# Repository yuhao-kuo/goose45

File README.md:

# Goose45

Goose45 is a 45% keyboard project.

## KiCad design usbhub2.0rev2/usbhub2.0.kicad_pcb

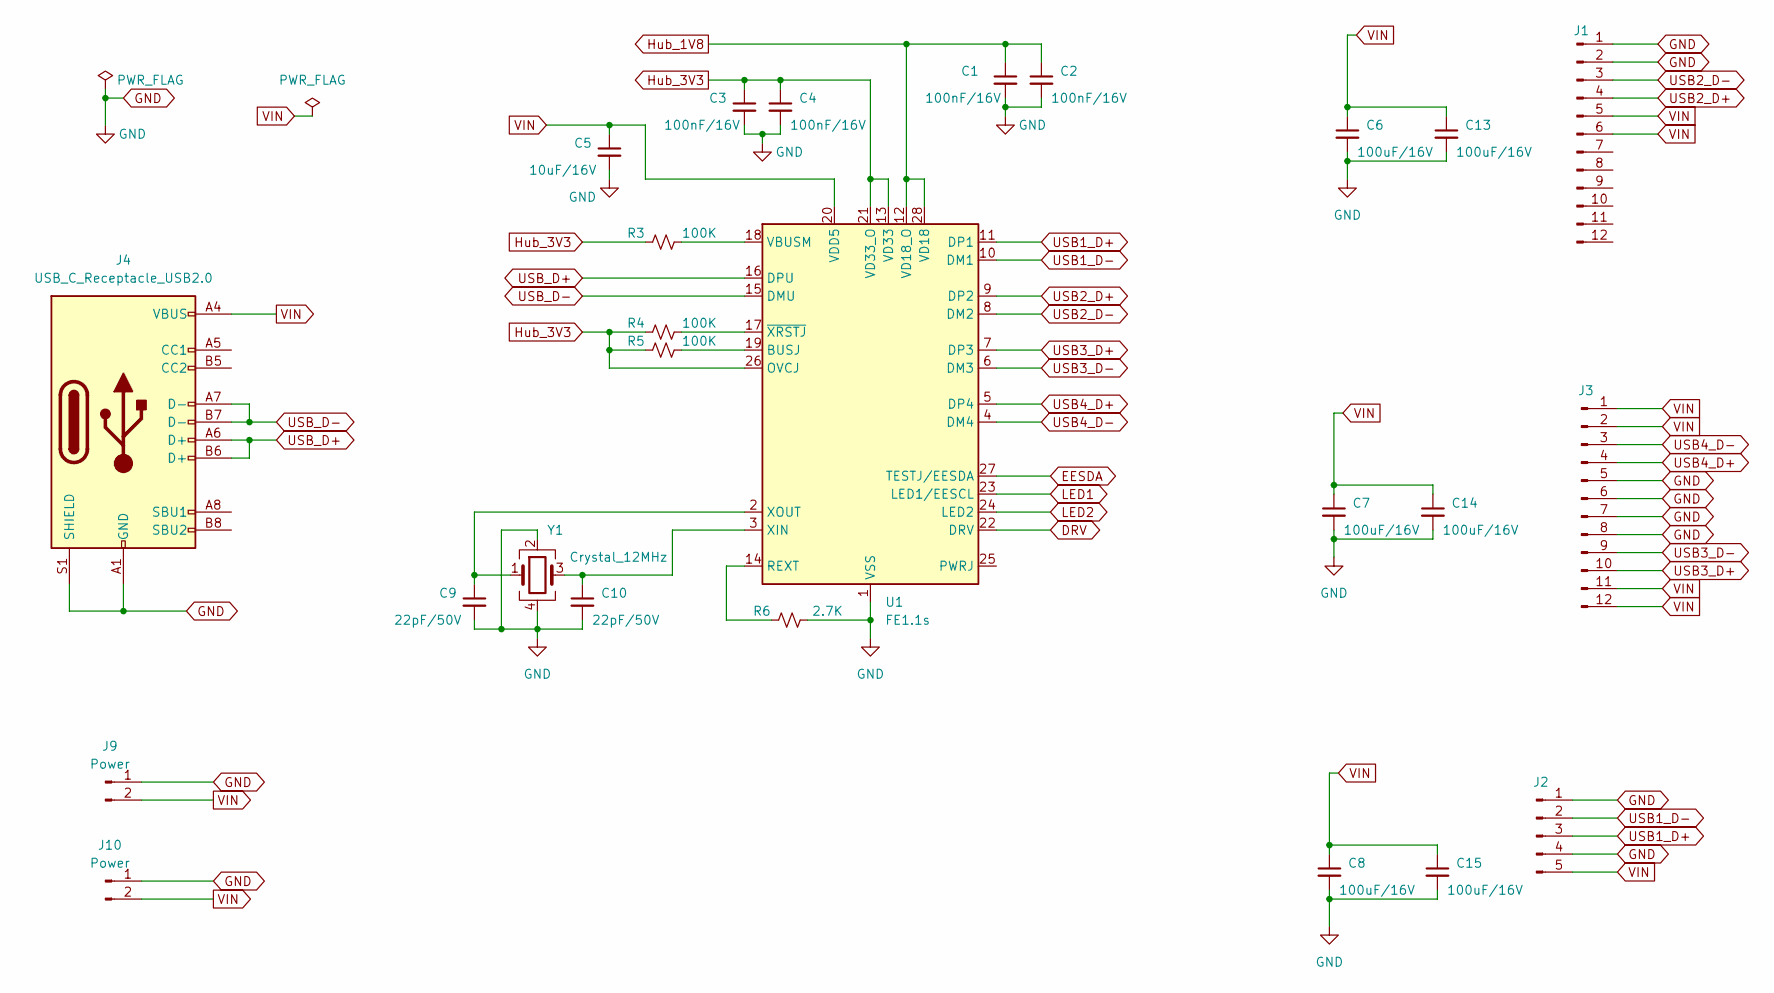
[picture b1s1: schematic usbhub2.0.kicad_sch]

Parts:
C1, C2, C3, C4: 100nF/16V; C_0603_1608Metric
C5: 10uF/16V; C_0603_1608Metric
C6, C7, C8: 100uF/16V; C_1206_3216Metric
C9, C10: 22pF/50V; C_0603_1608Metric
C13, C14, C15: 100uF/16V; CP_EIA-7343-30_AVX-N_Pad2.25x2.55mm_HandSolder
J1, J3: Conn_01x12_Pin; Hirose_FH12-12S-0.5SH_1x12-1MP_P0.50mm_Horizontal
J2: Conn_01x05_Male; PinHeader_1x05_P2.54mm_Vertical
J4: USB_C_Receptacle_USB2.0; USB_C_Receptacle_HRO_TYPE-C-31-M-12
J9, J10: Power; PinHeader_1x02_P2.54mm_Vertical
R3, R4, R5: 100K; R_0603_1608Metric
R6: 2.7K; R_0603_1608Metric
U1: FE1.1s; SSOP-28_3.9x9.9mm_P0.635mm
Y1: Crystal_12MHz; Crystal_SMD_Abracon_ABM3C-4Pin_5.0x3.2mm

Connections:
DRV: U1.22 (DRV)
EESDA: U1.27 (TESTJ/EESDA)
GND: C1.2, C2.2, C3.2, C4.2, C5.2, C6.2, C7.2, C8.2, C9.2, C10.2, C13.2, C14.2, C15.2, J1.1, J1.2, J2.1, J2.4, J3.5, J3.6, J3.7, J3.8, J4.A1 (GND), J4.A12 (GND), J4.B1 (GND), J4.B12 (GND), J4.S1 (SHIELD), J9.1, J10.1, R6.2, U1.1 (VSS), Y1.2, Y1.4
Hub_1V8: C1.1, C2.1, U1.12 (VD18_O), U1.28 (VD18)
Hub_3V3: C3.1, C4.1, R3.1, R4.1, R5.1, U1.13 (VD33), U1.21 (VD33_O), U1.26 (OVCJ)
LED1: U1.23 (LED1/EESCL)
LED2: U1.24 (LED2)
unnamed: R5.2, U1.19 (BUSJ)
unnamed: R6.1, U1.14 (REXT)
unnamed: R3.2, U1.18 (VBUSM)
unnamed: C10.1, U1.3 (XIN), Y1.3
unnamed: C9.1, U1.2 (XOUT), Y1.1
unnamed: R4.2, U1.17 (~XRSTJ)
USB1_D+: J2.3, U1.11 (DP1)
USB1_D-: J2.2, U1.10 (DM1)
USB2_D+: J1.4, U1.9 (DP2)
USB2_D-: J1.3, U1.8 (DM2)
USB3_D+: J3.10, U1.7 (DP3)
USB3_D-: J3.9, U1.6 (DM3)
USB4_D+: J3.4, U1.5 (DP4)
USB4_D-: J3.3, U1.4 (DM4)
USB_D+: J4.A6 (D+), J4.B6 (D+), U1.16 (DPU)
USB_D-: J4.A7 (D-), J4.B7 (D-), U1.15 (DMU)
VIN: C5.1, C6.1, C7.1, C8.1, C13.1, C14.1, C15.1, J1.5, J1.6, J2.5, J3.1, J3.2, J3.11, J3.12, J4.A4 (VBUS), J4.A9 (VBUS), J4.B4 (VBUS), J4.B9 (VBUS), J9.2, J10.2, U1.20 (VDD5)

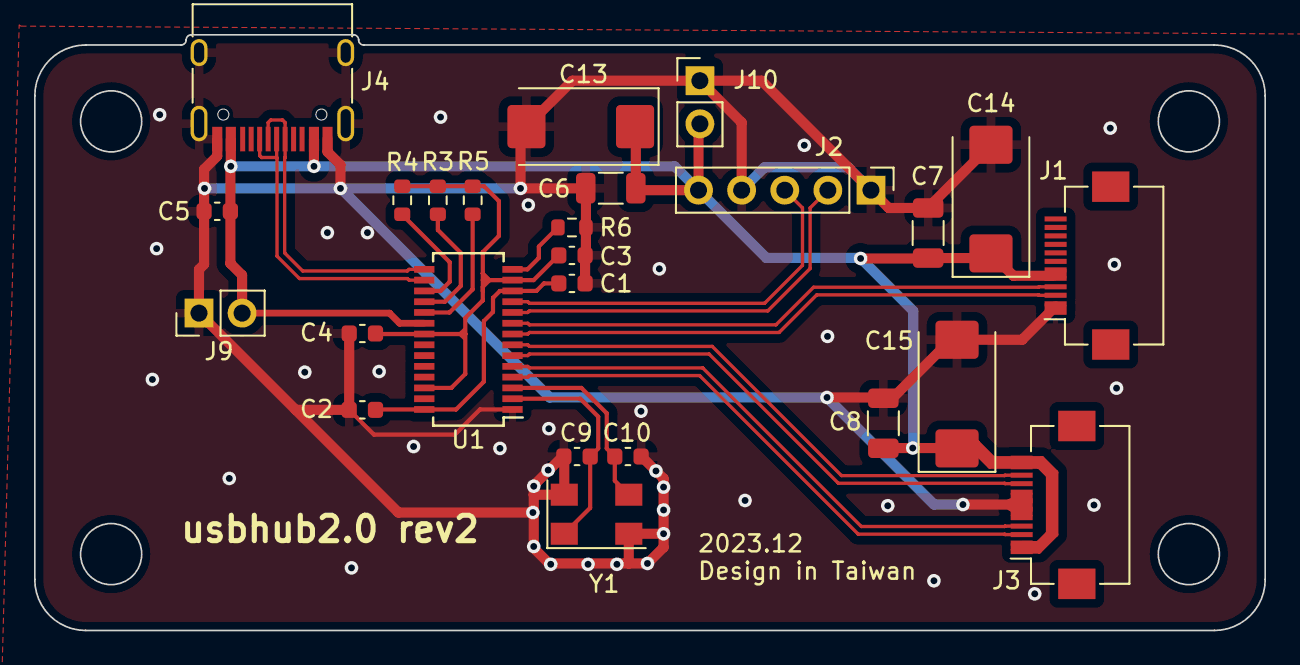
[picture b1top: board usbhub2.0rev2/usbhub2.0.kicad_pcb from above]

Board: 2 copper layers, 72.5 x 35.1 mm, 25 parts (0 on the bottom side), 20 nets.

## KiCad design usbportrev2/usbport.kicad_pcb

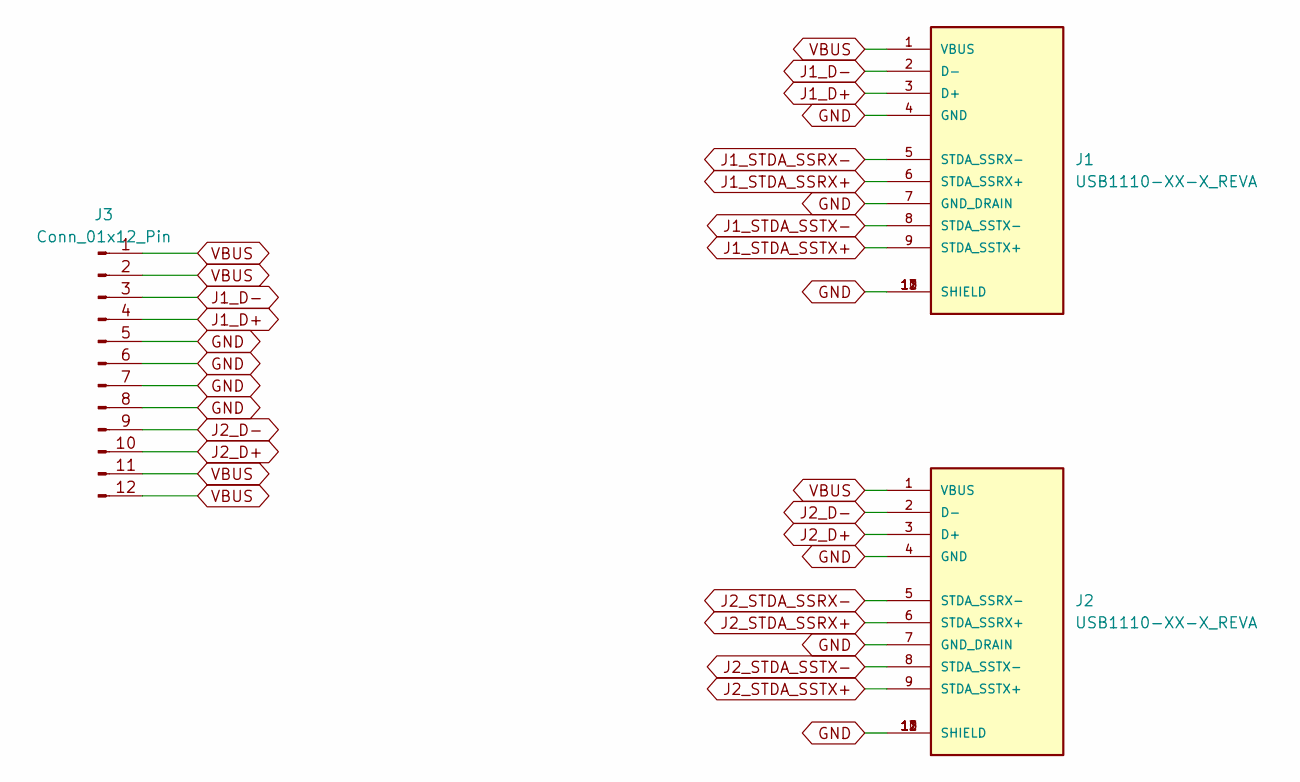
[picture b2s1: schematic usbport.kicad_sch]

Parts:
J1, J2: USB1110-XX-X_REVA; GCT_USB1110_goose45_usbport
J3: Conn_01x12_Pin; Hirose_FH12-12S-0.5SH_1x12-1MP_P0.50mm_Horizontal

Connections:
GND: J1.4 (GND), J1.7 (GND_DRAIN), J1.10 (SHIELD), J1.11 (SHIELD), J1.12 (SHIELD), J1.13 (SHIELD), J2.4 (GND), J2.7 (GND_DRAIN), J2.10 (SHIELD), J2.11 (SHIELD), J2.12 (SHIELD), J2.13 (SHIELD), J3.5, J3.6, J3.7, J3.8
J1_D+: J1.3 (D+), J3.4
J1_D-: J1.2 (D-), J3.3
J1_STDA_SSRX+: J1.6 (STDA_SSRX+)
J1_STDA_SSRX-: J1.5 (STDA_SSRX-)
J1_STDA_SSTX+: J1.9 (STDA_SSTX+)
J1_STDA_SSTX-: J1.8 (STDA_SSTX-)
J2_D+: J2.3 (D+), J3.10
J2_D-: J2.2 (D-), J3.9
J2_STDA_SSRX+: J2.6 (STDA_SSRX+)
J2_STDA_SSRX-: J2.5 (STDA_SSRX-)
J2_STDA_SSTX+: J2.9 (STDA_SSTX+)
J2_STDA_SSTX-: J2.8 (STDA_SSTX-)
VBUS: J1.1 (VBUS), J2.1 (VBUS), J3.1, J3.2, J3.11, J3.12

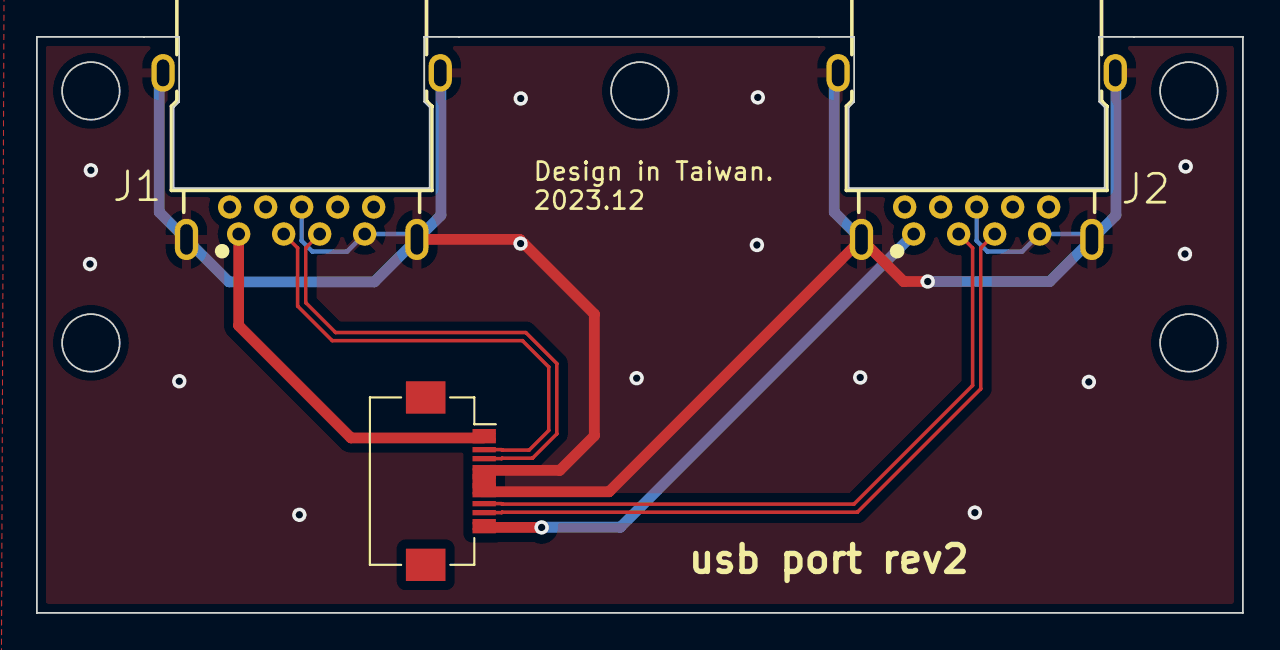
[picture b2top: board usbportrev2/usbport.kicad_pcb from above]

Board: 2 copper layers, 67.0 x 32.0 mm, 3 parts (0 on the bottom side), 6 nets.

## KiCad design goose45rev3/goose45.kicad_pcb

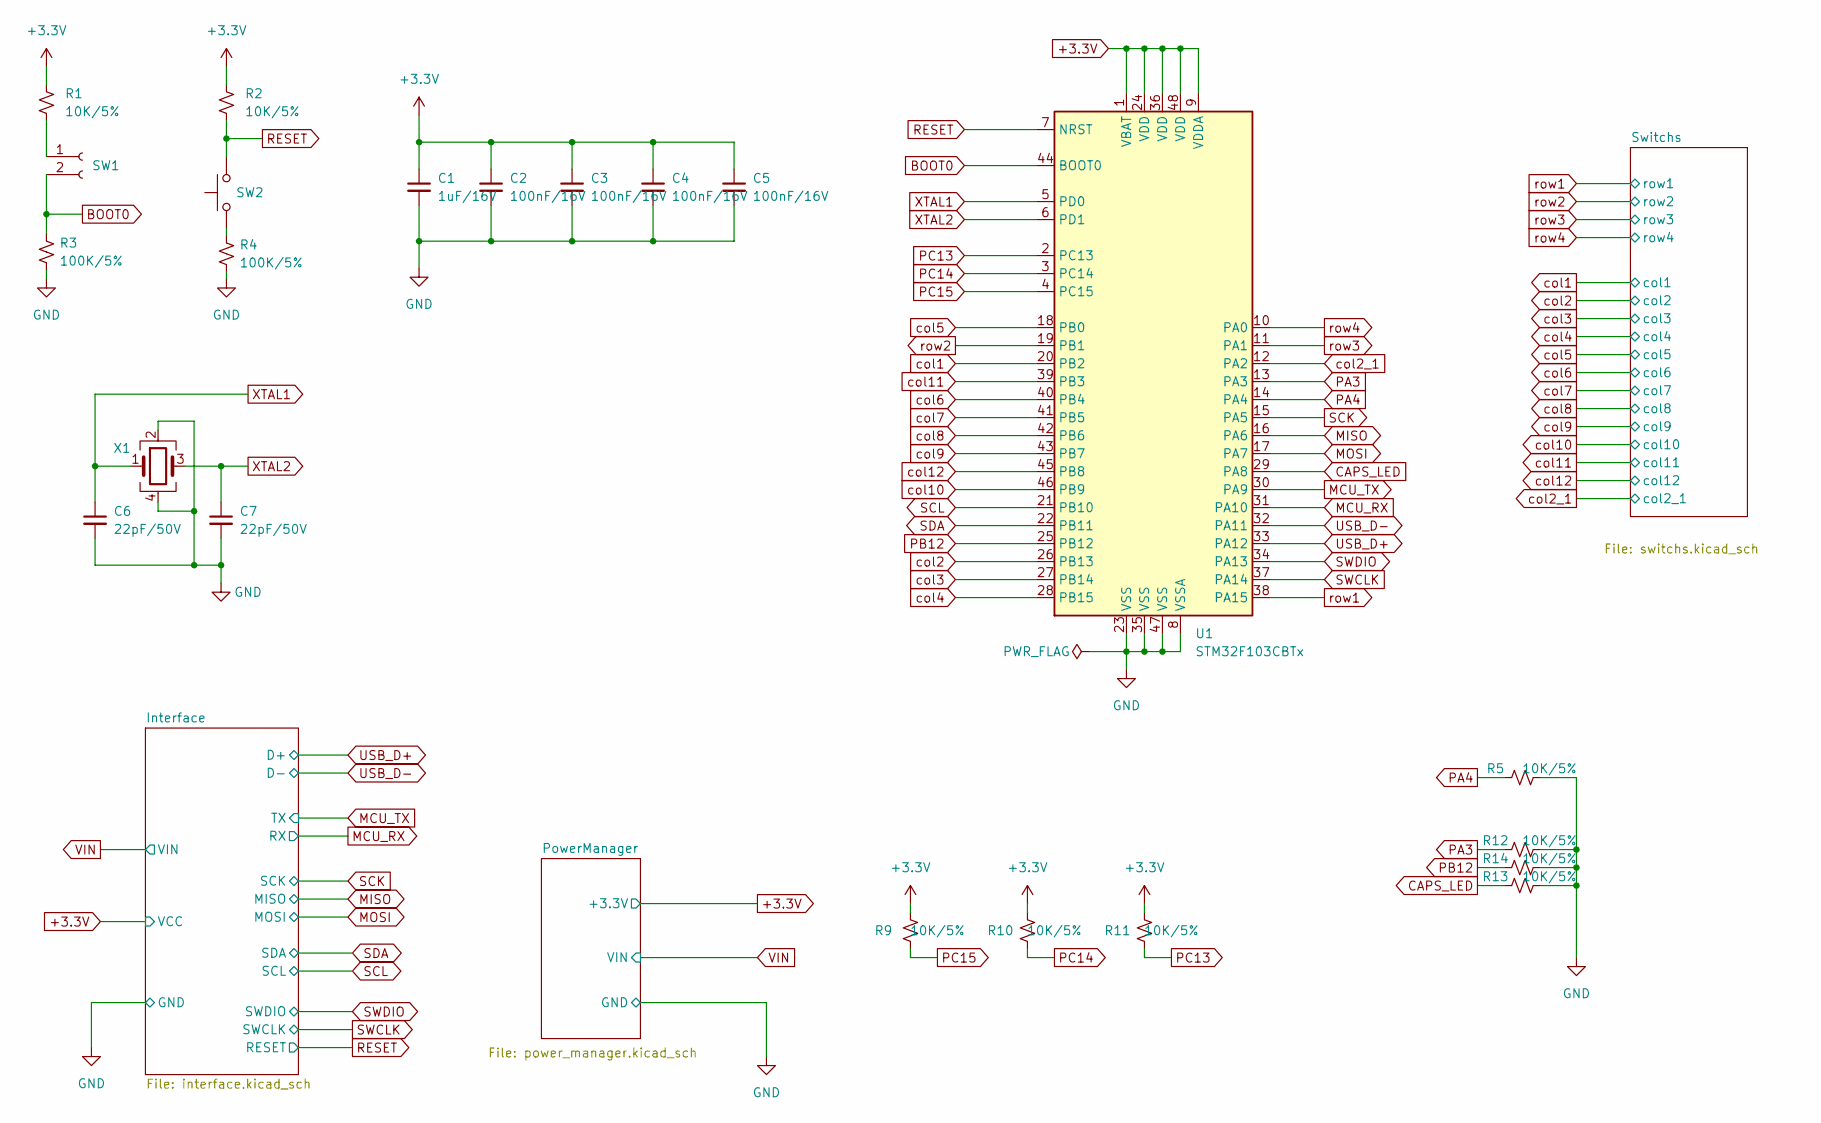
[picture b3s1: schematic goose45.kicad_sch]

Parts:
C1: 1uF/16V; C_0603_1608Metric
C2, C3, C4, C5: 100nF/16V; C_0603_1608Metric
C6, C7: 22pF/50V; C_0603_1608Metric
R1, R2, R5, R9, R10, R11, R12, R13, R14: 10K/5%; R_0603_1608Metric
R3, R4: 100K/5%; R_0603_1608Metric
SW1: Conn_01x02_Female; PinHeader_1x02_P2.00mm_Vertical
SW2: SW_Push; SW_Push_1P1T_NO_CK_KSC6xxJ
U1: STM32F103CBTx; LQFP-48_7x7mm_P0.5mm
X1: Crystal_GND24; Crystal_SMD_TXC_7M-4Pin_3.2x2.5mm

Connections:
+3.3V: C1.1, C2.1, C3.1, C4.1, C5.1, R1.1, R2.1, R9.1, R10.1, R11.1, U1.1 (VBAT), U1.9 (VDDA), U1.24 (VDD), U1.36 (VDD), U1.48 (VDD); also elsewhere on the board
BOOT0: R3.1, SW1.2, U1.44 (BOOT0)
CAPS_LED: R13.2, U1.29 (PA8)
GND: C1.2, C2.2, C3.2, C4.2, C5.2, C6.2, C7.2, R3.2, R4.2, R5.1, R12.1, R13.1, R14.1, U1.8 (VSSA), U1.23 (VSS), U1.35 (VSS), U1.47 (VSS), X1.2, X1.4; also elsewhere on the board
MCU_RX: U1.31 (PA10); also elsewhere on the board
MCU_TX: U1.30 (PA9); also elsewhere on the board
MISO: U1.16 (PA6); also elsewhere on the board
MOSI: U1.17 (PA7); also elsewhere on the board
unnamed: R4.1, SW2.1
unnamed: R1.2, SW1.1
PA3: R12.2, U1.13 (PA3)
PA4: R5.2, U1.14 (PA4)
PB12: R14.2, U1.25 (PB12)
PC13: R11.2, U1.2 (PC13)
PC14: R10.2, U1.3 (PC14)
PC15: R9.2, U1.4 (PC15)
RESET: R2.2, SW2.2, U1.7 (NRST); also elsewhere on the board
SCK: U1.15 (PA5); also elsewhere on the board
SCL: U1.21 (PB10); also elsewhere on the board
SDA: U1.22 (PB11); also elsewhere on the board
SWCLK: U1.37 (PA14); also elsewhere on the board
SWDIO: U1.34 (PA13); also elsewhere on the board
USB_D+: U1.33 (PA12); also elsewhere on the board
USB_D-: U1.32 (PA11); also elsewhere on the board
XTAL1: C6.1, U1.5 (PD0), X1.1
XTAL2: C7.1, U1.6 (PD1), X1.3
col1: U1.20 (PB2); also elsewhere on the board
col4: U1.28 (PB15); also elsewhere on the board
col5: U1.18 (PB0); also elsewhere on the board
col6: U1.40 (PB4); also elsewhere on the board
col7: U1.41 (PB5); also elsewhere on the board
col8: U1.42 (PB6); also elsewhere on the board
col10: U1.46 (PB9); also elsewhere on the board
col11: U1.39 (PB3); also elsewhere on the board
col12: U1.45 (PB8); also elsewhere on the board
row1: U1.38 (PA15); also elsewhere on the board
row2: U1.19 (PB1); also elsewhere on the board
row3: U1.11 (PA1); also elsewhere on the board
row4: U1.10 (PA0); also elsewhere on the board

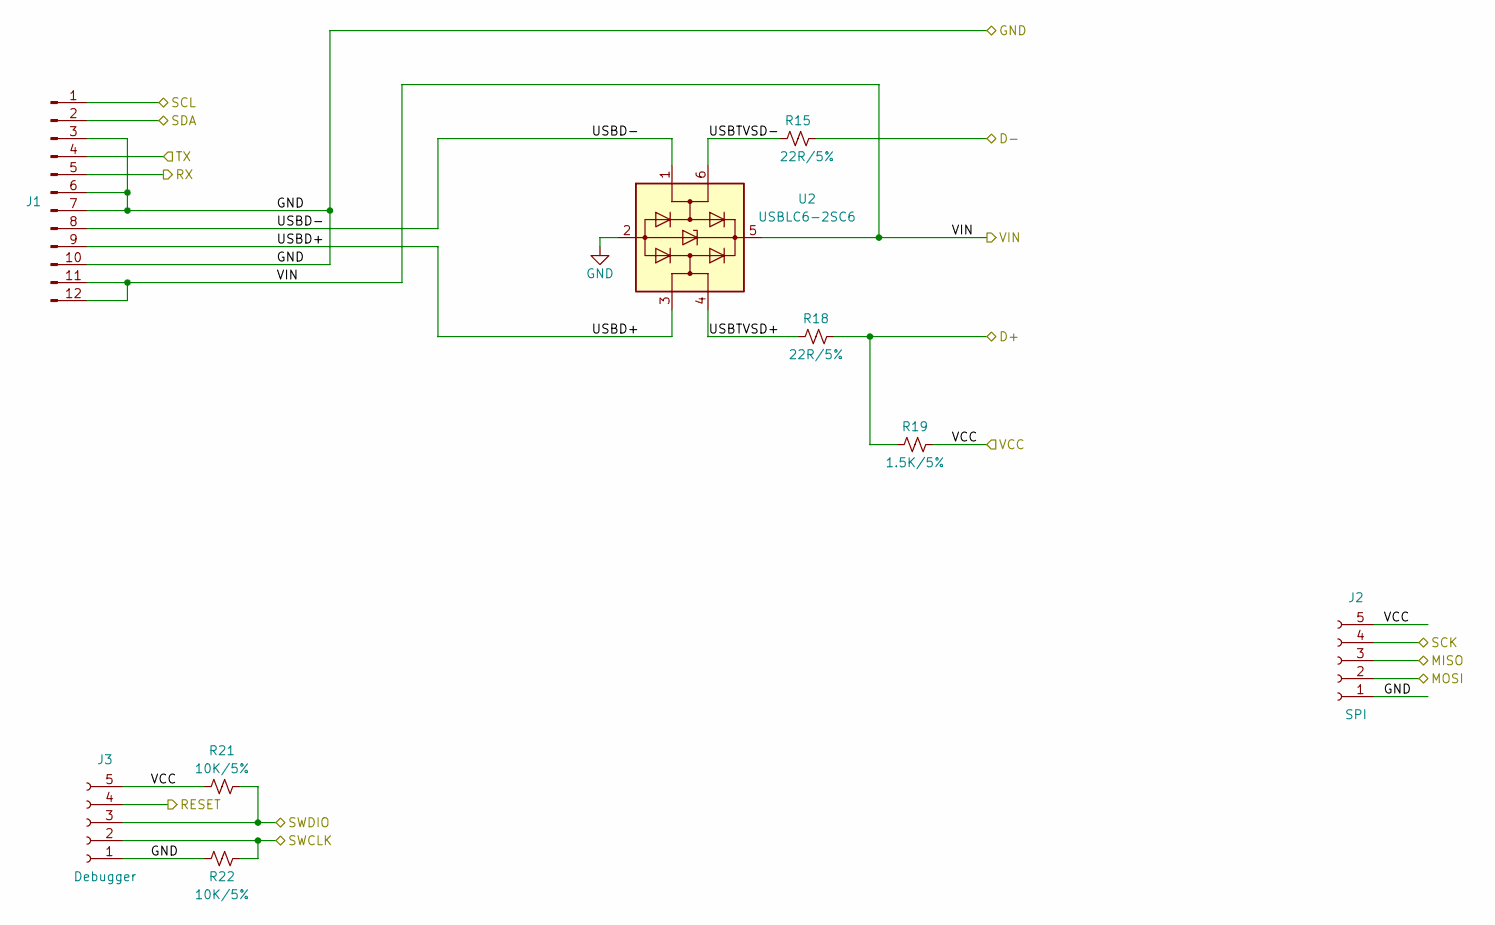
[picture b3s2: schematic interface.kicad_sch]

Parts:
J1: USB connector; Hirose_FH12-12S-0.5SH_1x12-1MP_P0.50mm_Horizontal
J2: SPI; PinHeader_1x05_P2.00mm_Vertical
J3: Debugger; PinHeader_1x05_P2.00mm_Vertical
R15, R18: 22R/5%; R_0603_1608Metric
R19: 1.5K/5%; R_0603_1608Metric
R21, R22: 10K/5%; R_0603_1608Metric
U2: USBLC6-2SC6; SOT-23-6

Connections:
+3.3V: J2.5, J3.5, R19.2, R21.1; also elsewhere on the board
/Interface/USBD+: J1.9, U2.3 (I/O2)
/Interface/USBD-: J1.8, U2.1 (I/O1)
/Interface/USBTVSD+: R18.1, U2.4 (I/O2)
/Interface/USBTVSD-: R15.1, U2.6 (I/O1)
GND: J1.3, J1.6, J1.7, J1.10, J2.1, J3.1, R22.1, U2.2 (GND); also elsewhere on the board
MCU_RX: J1.5; also elsewhere on the board
MCU_TX: J1.4; also elsewhere on the board
MISO: J2.3; also elsewhere on the board
MOSI: J2.2; also elsewhere on the board
RESET: J3.4; also elsewhere on the board
SCK: J2.4; also elsewhere on the board
SCL: J1.1; also elsewhere on the board
SDA: J1.2; also elsewhere on the board
SWCLK: J3.2, R22.2; also elsewhere on the board
SWDIO: J3.3, R21.2; also elsewhere on the board
USB_D+: R18.2, R19.1; also elsewhere on the board
USB_D-: R15.2; also elsewhere on the board
VIN: J1.11, J1.12, U2.5 (VBUS); also elsewhere on the board

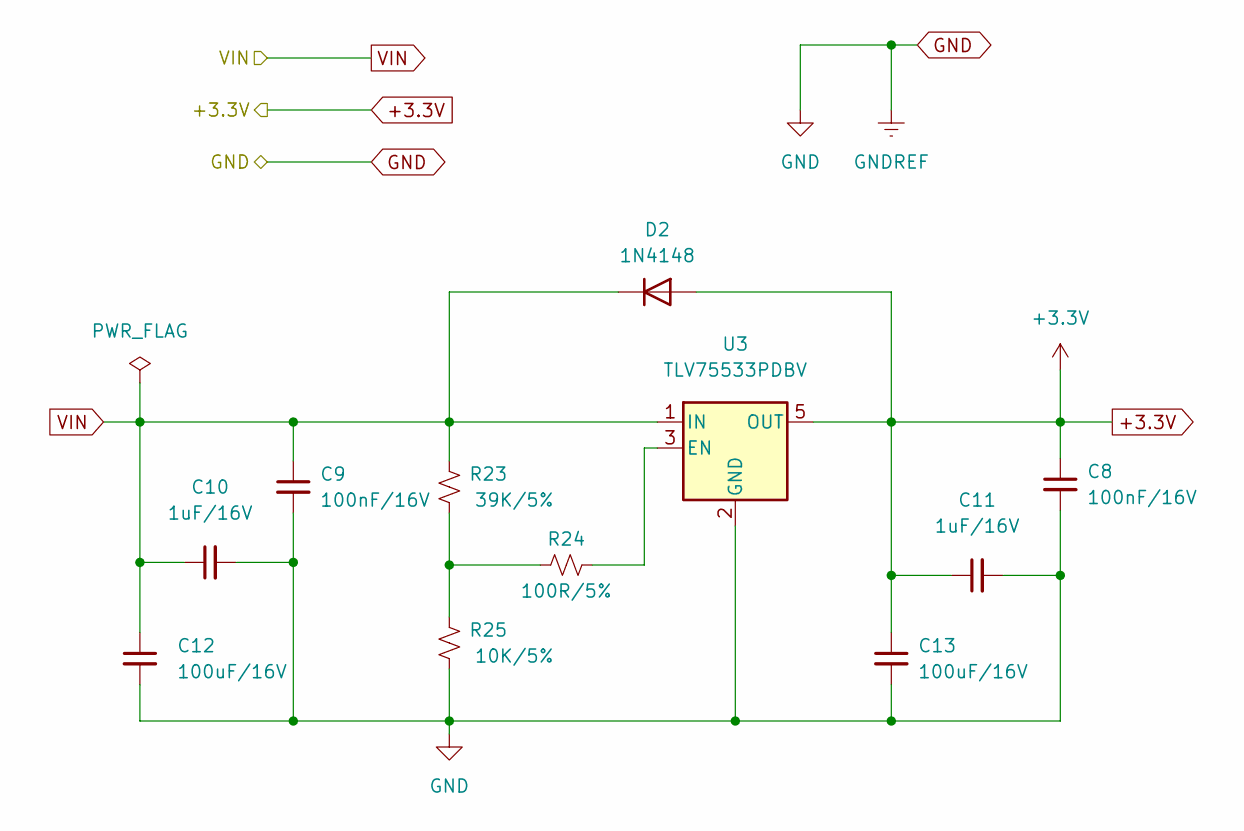
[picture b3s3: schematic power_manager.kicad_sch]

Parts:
C8, C9: 100nF/16V; C_0603_1608Metric
C10, C11: 1uF/16V; C_0603_1608Metric
C12, C13: 100uF/16V; C_0603_1608Metric
D2: 1N4148; D_SOD-323
R23: 39K/5%; R_0603_1608Metric
R24: 100R/5%; R_0603_1608Metric
R25: 10K/5%; R_0603_1608Metric
U3: TLV75533PDBV; SOT-23-5

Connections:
+3.3V: C8.1, C11.1, C13.1, D2.2 (A), U3.5 (OUT); also elsewhere on the board
GND: C8.2, C9.2, C10.2, C11.2, C12.2, C13.2, R25.2, U3.2 (GND); also elsewhere on the board
unnamed: R23.1, R24.2, R25.1
unnamed: R24.1, U3.3 (EN)
VIN: C9.1, C10.1, C12.1, D2.1 (K), R23.2, U3.1 (IN); also elsewhere on the board

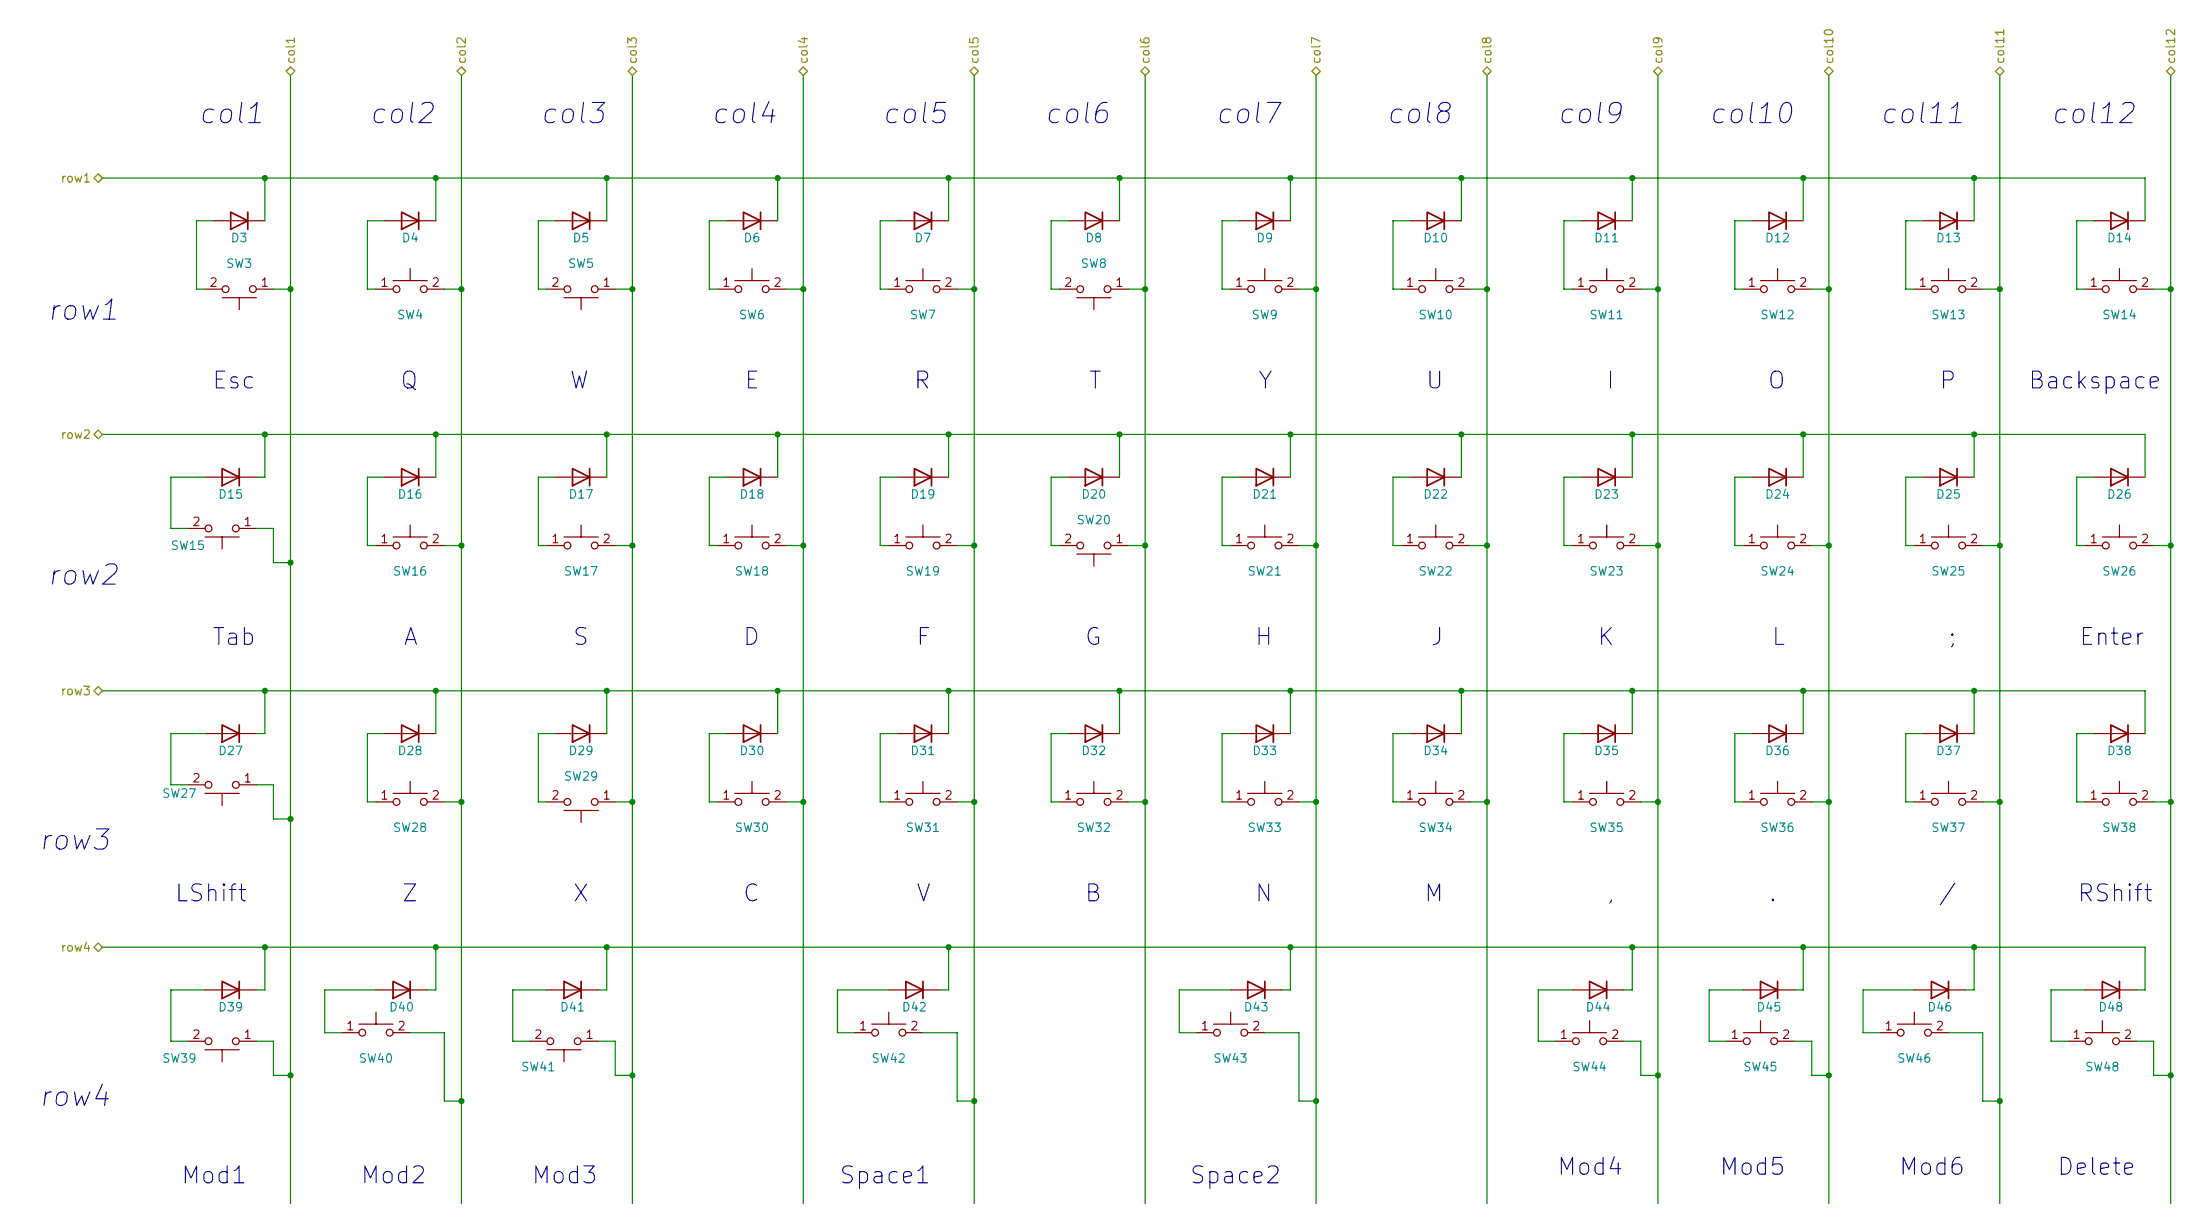
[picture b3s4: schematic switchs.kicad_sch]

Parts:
D3, D4, D5, D6, D7, D8, D9, D10, D11, D12, D13, D14, D15, D16, D17, D18, D19, D20, D21, D22, D23, D24, D25, D26, D27, D28, D29, D30, D31, D32, D33, D34, D35, D36, D37, D38, D39, D40, D41, D42, D43, D44, D45, D46, D48: 1N4148; D_0805_2012Metric
SW3, SW4, SW5, SW6, SW7, SW8, SW9, SW10, SW11, SW12, SW13, SW14, SW15, SW16, SW17, SW18, SW19, SW20, SW21, SW22, SW23, SW24, SW25, SW26, SW27, SW28, SW29, SW30, SW31, SW32, SW33, SW34, SW35, SW36, SW37, SW38, SW39, SW40, SW41, SW42, SW43, SW44, SW45, SW46, SW48: SW_Push; SW_Hotswap_Kailh_MX

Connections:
unnamed: D3.2 (A), SW3.2
unnamed: D4.2 (A), SW4.1
unnamed: D5.2 (A), SW5.2
unnamed: D6.2 (A), SW6.1
unnamed: D7.2 (A), SW7.1
unnamed: D8.2 (A), SW8.2
unnamed: D9.2 (A), SW9.1
unnamed: D10.2 (A), SW10.1
unnamed: D11.2 (A), SW11.1
unnamed: D12.2 (A), SW12.1
unnamed: D13.2 (A), SW13.1
unnamed: D14.2 (A), SW14.1
unnamed: D15.2 (A), SW15.2
unnamed: D16.2 (A), SW16.1
unnamed: D17.2 (A), SW17.1
unnamed: D18.2 (A), SW18.1
unnamed: D19.2 (A), SW19.1
unnamed: D20.2 (A), SW20.2
unnamed: D21.2 (A), SW21.1
unnamed: D22.2 (A), SW22.1
unnamed: D23.2 (A), SW23.1
unnamed: D24.2 (A), SW24.1
unnamed: D25.2 (A), SW25.1
unnamed: D26.2 (A), SW26.1
unnamed: D27.2 (A), SW27.2
unnamed: D28.2 (A), SW28.1
unnamed: D29.2 (A), SW29.2
unnamed: D30.2 (A), SW30.1
unnamed: D31.2 (A), SW31.1
unnamed: D32.2 (A), SW32.1
unnamed: D33.2 (A), SW33.1
unnamed: D34.2 (A), SW34.1
unnamed: D35.2 (A), SW35.1
unnamed: D36.2 (A), SW36.1
unnamed 46: D37.2 (A), SW37.1; also elsewhere on the board
unnamed 47: D38.2 (A), SW38.1; also elsewhere on the board
unnamed 48: D39.2 (A), SW39.2; also elsewhere on the board
unnamed 49: D40.2 (A), SW40.1; also elsewhere on the board
unnamed: D42.2 (A), SW42.1
unnamed: D43.2 (A), SW43.1
unnamed: D45.2 (A), SW45.1
unnamed: D46.2 (A), SW46.1
unnamed: D48.2 (A), SW48.1
col1: SW3.1, SW15.1, SW27.1, SW39.1; also elsewhere on the board
col4: SW6.2, SW18.2, SW30.2; also elsewhere on the board
col5: SW7.2, SW19.2, SW31.2, SW42.2; also elsewhere on the board
col6: SW8.1, SW20.1, SW32.2; also elsewhere on the board
col7: SW9.2, SW21.2, SW33.2, SW43.2; also elsewhere on the board
col8: SW10.2, SW22.2, SW34.2; also elsewhere on the board
col10: SW12.2, SW24.2, SW36.2, SW45.2; also elsewhere on the board
col11: SW13.2, SW25.2, SW37.2, SW46.2; also elsewhere on the board
col12: SW14.2, SW26.2, SW38.2, SW48.2; also elsewhere on the board
row1: D3.1 (K), D4.1 (K), D5.1 (K), D6.1 (K), D7.1 (K), D8.1 (K), D9.1 (K), D10.1 (K), D11.1 (K), D12.1 (K), D13.1 (K), D14.1 (K); also elsewhere on the board
row2: D15.1 (K), D16.1 (K), D17.1 (K), D18.1 (K), D19.1 (K), D20.1 (K), D21.1 (K), D22.1 (K), D23.1 (K), D24.1 (K), D25.1 (K), D26.1 (K); also elsewhere on the board
row3: D27.1 (K), D28.1 (K), D29.1 (K), D30.1 (K), D31.1 (K), D32.1 (K), D33.1 (K), D34.1 (K), D35.1 (K), D36.1 (K), D37.1 (K), D38.1 (K); also elsewhere on the board
row4: D39.1 (K), D40.1 (K), D41.1 (K), D42.1 (K), D43.1 (K), D44.1 (K), D45.1 (K), D46.1 (K), D48.1 (K); also elsewhere on the board

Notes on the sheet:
Backspace
col7
col8
col9
Mod1
col12
col2
Space2
Mod5
Tab
col11
LShift
row2
Mod4
Mod2
col5
Delete
Mod6
col10
row3
RShift
col1
Esc
col3
col4
row1
Enter
col6
Mod3
row4
Space1

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
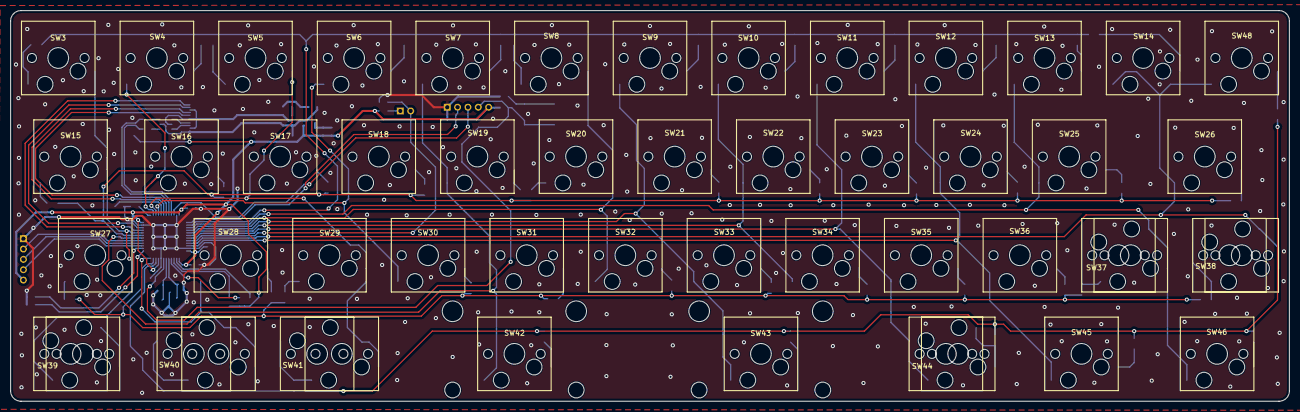
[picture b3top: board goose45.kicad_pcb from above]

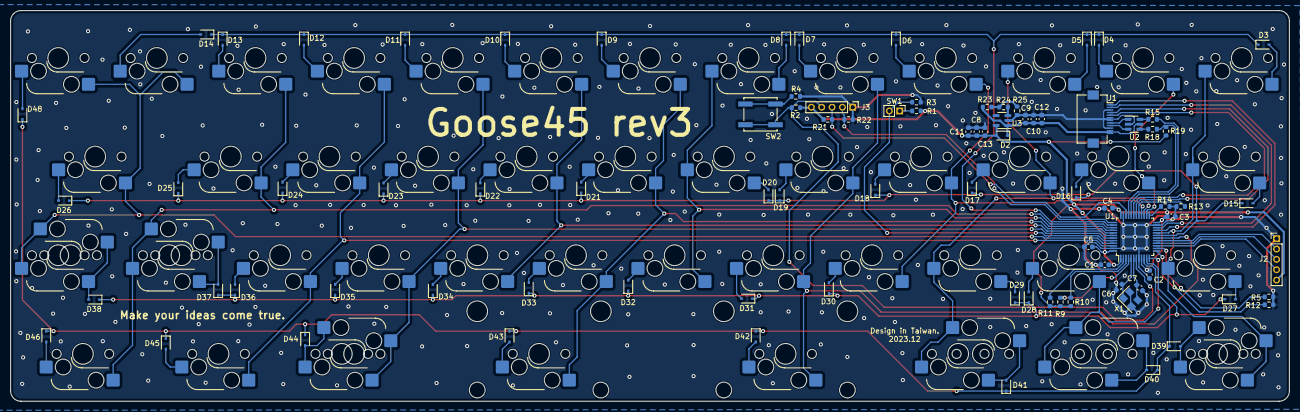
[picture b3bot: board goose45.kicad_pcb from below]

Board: 2 copper layers, 247.0 x 75.4 mm, 140 parts (87 on the bottom side), 95 nets.

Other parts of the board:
REF1, REF2: Stabilizer_Cherry_MX_2.00u
SW37_1, SW38_1, SW39_1, SW40_1, SW41_1, SW44_1: SW_Push; SW_Hotswap_Kailh_MX

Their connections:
unnamed 46: SW37_1.2; also elsewhere on the board
unnamed 47: SW38_1.2; also elsewhere on the board
unnamed 48: SW39_1.1; also elsewhere on the board
unnamed 49: SW40_1.2; also elsewhere on the board
col1: SW39_1.2; also elsewhere on the board
col11: SW37_1.1; also elsewhere on the board
col12: SW38_1.1; also elsewhere on the board

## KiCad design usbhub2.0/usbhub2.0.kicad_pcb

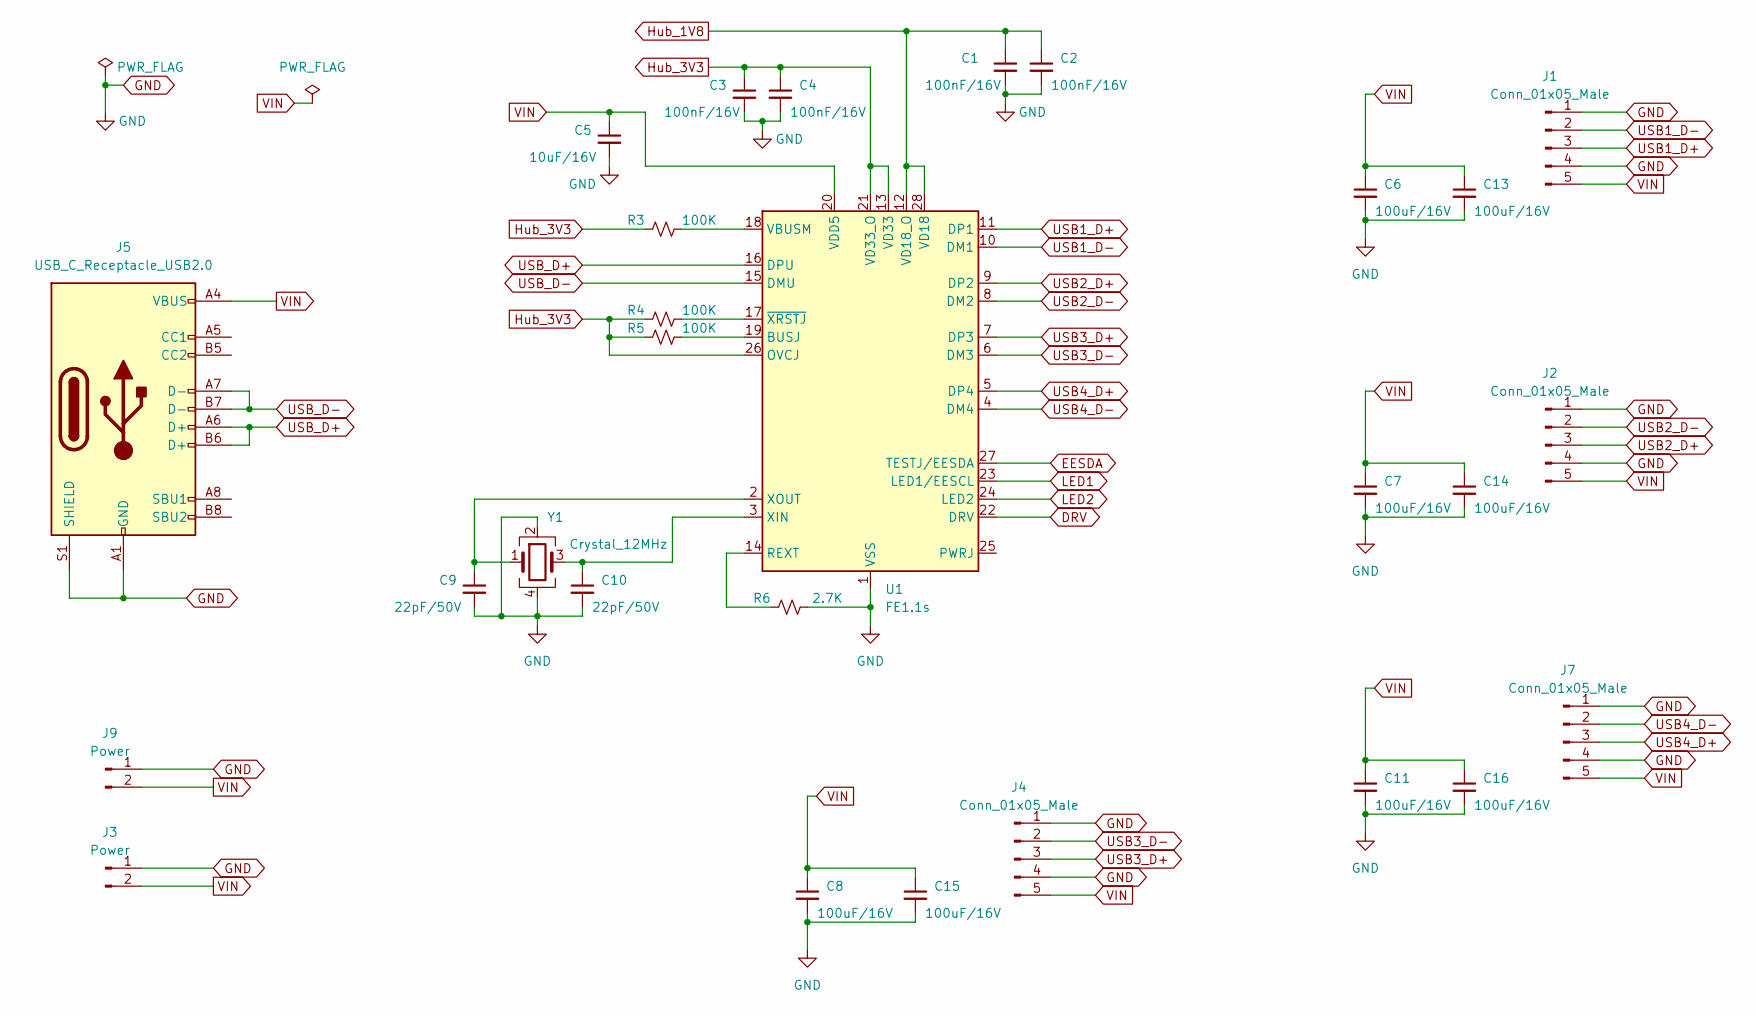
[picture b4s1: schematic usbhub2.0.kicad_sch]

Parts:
C1, C2, C3, C4: 100nF/16V; C_0603_1608Metric
C5: 10uF/16V; C_0603_1608Metric
C6, C7, C8, C11: 100uF/16V; C_1206_3216Metric
C9, C10: 22pF/50V; C_0603_1608Metric
C13, C14, C15, C16: 100uF/16V; CP_EIA-7343-30_AVX-N_Pad2.25x2.55mm_HandSolder
J1: Conn_01x05_Male; PinHeader_1x05_P2.00mm_Vertical
J2, J4, J7: Conn_01x05_Male; Molex_PicoBlade_53261-0571_1x05-1MP_P1.25mm_Horizontal
J3, J9: Power; PinHeader_1x02_P2.54mm_Vertical
J5: USB_C_Receptacle_USB2.0; USB_C_Receptacle_HRO_TYPE-C-31-M-12
R3, R4, R5: 100K; R_0603_1608Metric
R6: 2.7K; R_0603_1608Metric
U1: FE1.1s; SSOP-28_3.9x9.9mm_P0.635mm
Y1: Crystal_12MHz; Crystal_SMD_Abracon_ABM3C-4Pin_5.0x3.2mm

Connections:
DRV: U1.22 (DRV)
EESDA: U1.27 (TESTJ/EESDA)
GND: C1.2, C2.2, C3.2, C4.2, C5.2, C6.2, C7.2, C8.2, C9.2, C10.2, C11.2, C13.2, C14.2, C15.2, C16.2, J1.1, J1.4, J2.1, J2.4, J2.MP, J3.1, J4.1, J4.4, J4.MP, J5.A1 (GND), J5.A12 (GND), J5.B1 (GND), J5.B12 (GND), J5.S1 (SHIELD), J7.1, J7.4, J7.MP, J9.1, R6.2, U1.1 (VSS), Y1.2, Y1.4
Hub_1V8: C1.1, C2.1, U1.12 (VD18_O), U1.28 (VD18)
Hub_3V3: C3.1, C4.1, R3.1, R4.1, R5.1, U1.13 (VD33), U1.21 (VD33_O), U1.26 (OVCJ)
LED1: U1.23 (LED1/EESCL)
LED2: U1.24 (LED2)
unnamed: C9.1, U1.2 (XOUT), Y1.1
unnamed: C10.1, U1.3 (XIN), Y1.3
unnamed: R3.2, U1.18 (VBUSM)
unnamed: R4.2, U1.17 (~XRSTJ)
unnamed: R5.2, U1.19 (BUSJ)
unnamed: R6.1, U1.14 (REXT)
USB1_D+: J1.3, U1.11 (DP1)
USB1_D-: J1.2, U1.10 (DM1)
USB2_D+: J2.3, U1.9 (DP2)
USB2_D-: J2.2, U1.8 (DM2)
USB3_D+: J4.3, U1.7 (DP3)
USB3_D-: J4.2, U1.6 (DM3)
USB4_D+: J7.3, U1.5 (DP4)
USB4_D-: J7.2, U1.4 (DM4)
USB_D+: J5.A6 (D+), J5.B6 (D+), U1.16 (DPU)
USB_D-: J5.A7 (D-), J5.B7 (D-), U1.15 (DMU)
VIN: C5.1, C6.1, C7.1, C8.1, C11.1, C13.1, C14.1, C15.1, C16.1, J1.5, J2.5, J3.2, J4.5, J5.A4 (VBUS), J5.A9 (VBUS), J5.B4 (VBUS), J5.B9 (VBUS), J7.5, J9.2, U1.20 (VDD5)
